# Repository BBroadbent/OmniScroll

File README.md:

# OmniScroll

**OmniScroll** is an open-source, ultra-smooth desktop scroll wheel designed for precise CAD navigation, timeline scrub control, and high-speed document scrolling. 

By utilizing a large-diameter thin-section bearing and an off-axis magnetic rotary encoder, FluxDial achieves an effortless flywheel spin with zero axis wobble.

---

## Key Features

* **Flywheel Momentum:** Utilizes an `S6808` hybrid ceramic bearing ($40 \times 52 \times 7\text{ mm}$) stripped of grease for near-zero rotational resistance.
* **Magnetic Angle Sensing:** High-resolution rotary encoder (AS5600 / MA730) for smooth, non-contact position tracking.
* **Zero Axis Play:** Large-bore thin-section design houses internal electronics inside the hollow core, lowering the center of gravity and eliminating side-to-side wobble.
* **Custom Control Curves:** Configurable firmware supporting variable-speed scroll acceleration, granular scrub modes, and custom macro actions.

---

## Hardware Assembly

### Bill of Materials (BOM)

| Component | Specification / Part | Qty | Notes |
| :--- | :--- | :--- | :--- |
| **Main Bearing** | `S6808-2RS` Hybrid Ceramic ($40 \times 52 \times 7\text{ mm}$) | 1 | Degreased with IPA for maximum free-spin |
| **Magnetic Encoder** | AS5600 or MA730 PCB Module | 1 | Mounts coaxially inside the inner ring |
| **Diametral Magnet** | $6\text{ mm} \times 2.5\text{ mm}$ N35 (Diametrically Magnetized) | 1 | Fixed to the rotating outer knob shaft |
| **Microcontroller** | Raspberry Pi Pico / Seeed XIAO (RP2040) | 1 | Compact form factor fits inside housing base |
| **Enclosure** | 3D Printed (PLA/PETG) or Machined Aluminum | 1 | Files provided in `/cad` |

---

## Getting Started

### 1. Bearing Preparation
1. Carefully pop off the rubber seals (`2RS`) on the `S6808` bearing.
2. Submerge in isopropyl alcohol (IPA) and spin thoroughly to strip factory grease.
3. Blow dry with compressed air. (Optional: Apply 1 drop of high-speed instrument oil for quieter operation).

### 2. Firmware Setup
1. Clone this repository:
   ```bash
   git clone [https://github.com/your-username/FluxDial.git](https://github.com/your-username/FluxDial.git)

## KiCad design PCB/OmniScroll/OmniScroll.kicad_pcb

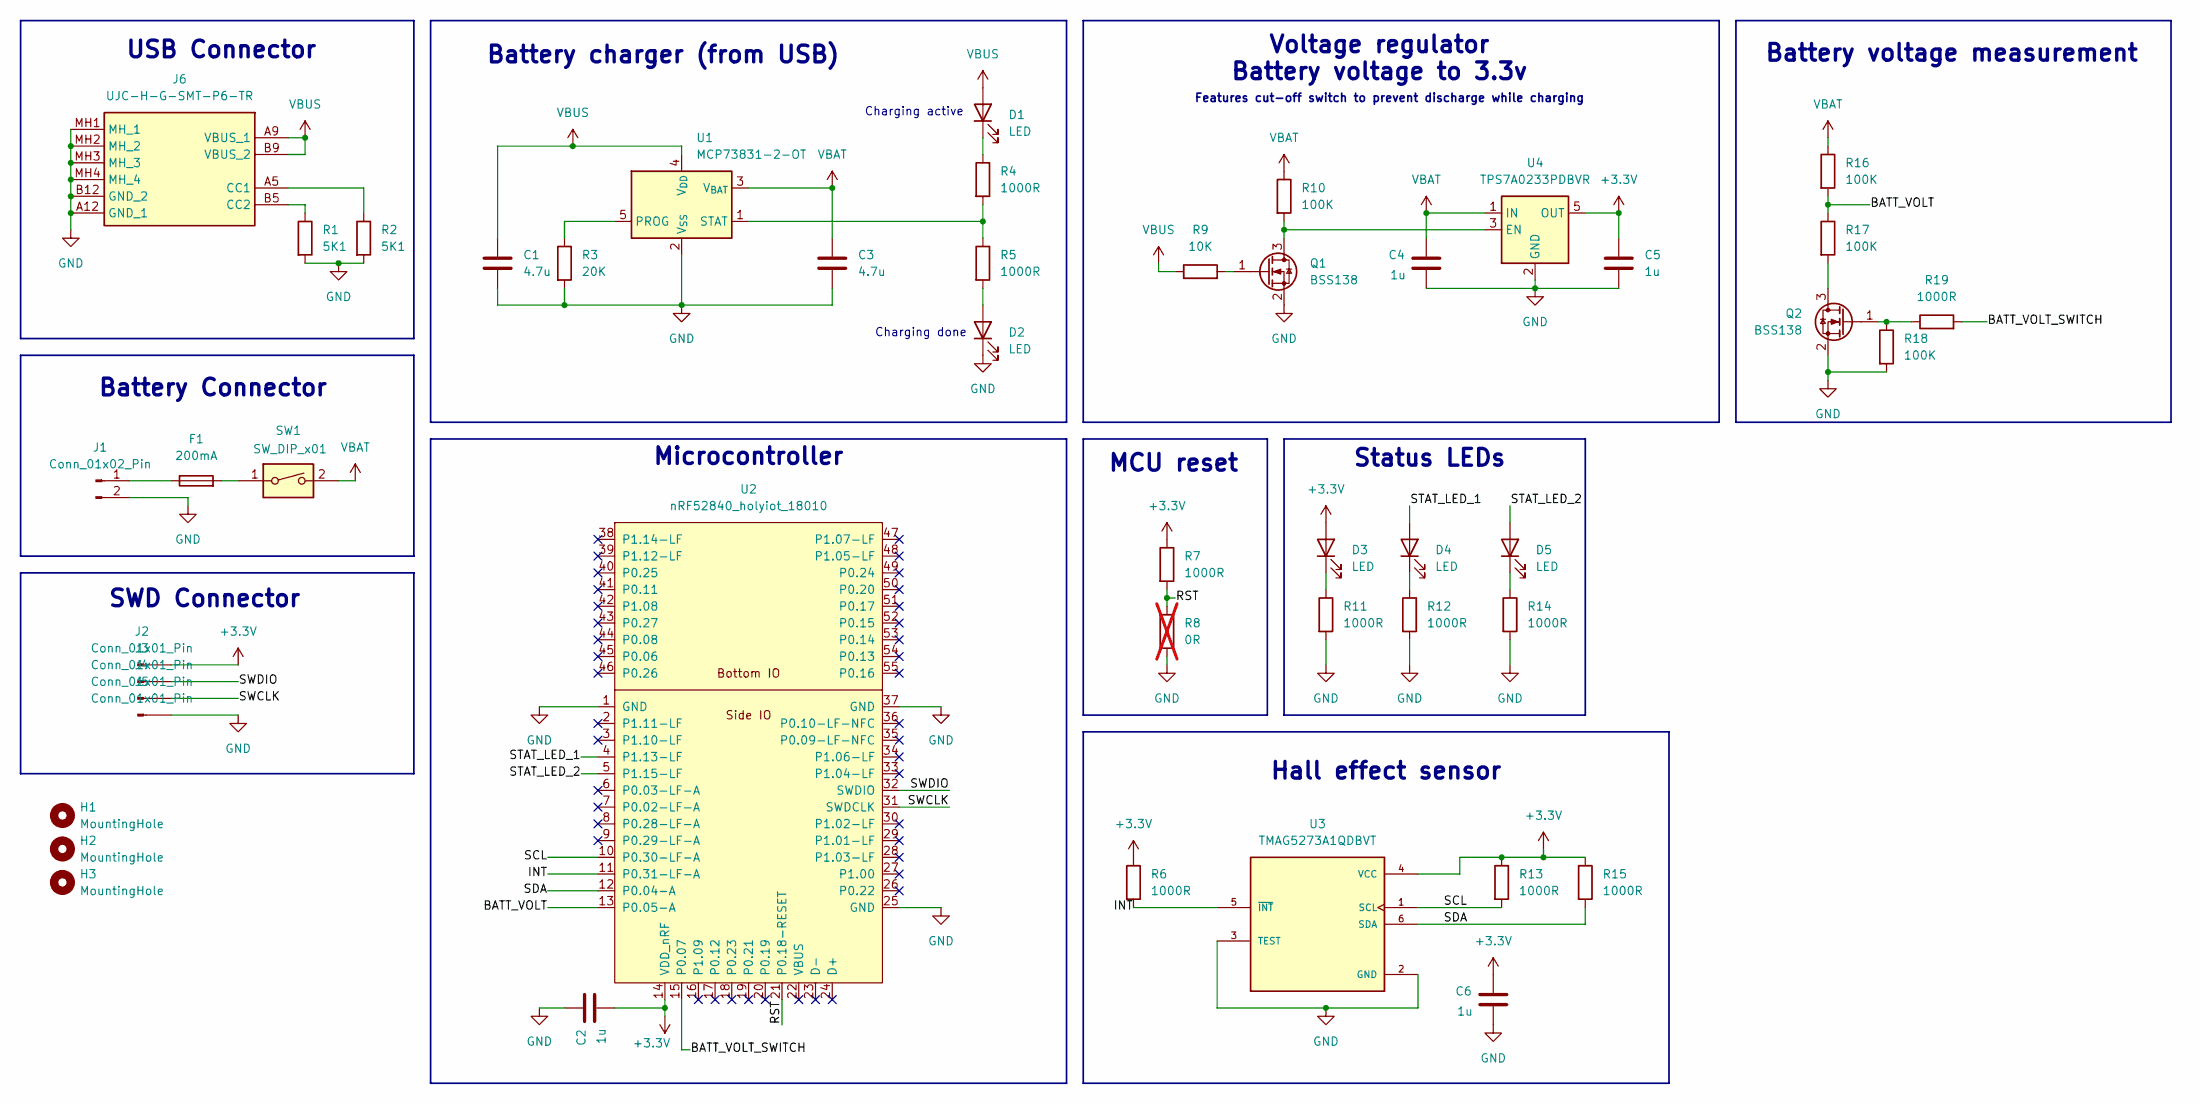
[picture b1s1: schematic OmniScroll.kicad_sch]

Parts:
C1, C3: 4.7u; C_0603_1608Metric_Pad1.08x0.95mm_HandSolder
C2, C4, C5, C6: 1u; C_0603_1608Metric_Pad1.08x0.95mm_HandSolder
D1, D2, D3, D4, D5: LED; LED_0603_1608Metric_Pad1.05x0.95mm_HandSolder
F1: 200mA; R_0603_1608Metric_Pad0.98x0.95mm_HandSolder
H1, H2, H3: MountingHole; MountingHole_2.2mm_M2_DIN965_Pad
J1: Conn_01x02_Pin; Molex_PicoBlade_53048-0210_1x02_P1.25mm_Horizontal
J2, J3, J4, J5: Conn_01x01_Pin; TestPoint_Pad_D1.5mm
J6: UJC-H-G-SMT-P6-TR; UJCHGSMTP6TR; Manufacturer_Part_Number UJC-H-G-SMT-P6-TR; Mouser Part Number 179-UJCHGSMTP6TR
Q1, Q2: BSS138; SOT-23
R1, R2: 5K1; R_0603_1608Metric_Pad0.98x0.95mm_HandSolder
R3: 20K; R_0603_1608Metric_Pad0.98x0.95mm_HandSolder
R4, R5, R6, R7, R11, R12, R13, R14, R15, R19: 1000R; R_0603_1608Metric_Pad0.98x0.95mm_HandSolder
R8: 0R; R_0402_1005Metric_Pad0.72x0.64mm_HandSolder; not fitted
R9: 10K; R_0603_1608Metric_Pad0.98x0.95mm_HandSolder
R10, R16, R17, R18: 100K; R_0603_1608Metric_Pad0.98x0.95mm_HandSolder
SW1: SW_DIP_x01; SW_DIP_SPSTx01_Slide_6.7x4.1mm_W8.61mm_P2.54mm_LowProfile
U1: MCP73831-2-OT; SOT-23-5
U2: nRF52840_holyiot_18010
U3: TMAG5273A1QDBVT; SOT95P280X140-6N; PARTREV B
U4: TPS7A0233PDBVR; SOT-23-5

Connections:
+3.3V: C2.2, C5.1, C6.1, D3.2 (A), J2.1 (Pin_1_1), R6.1, R7.1, R13.1, R15.1, U2.14 (VDD_nRF), U3.4 (VCC), U4.5 (OUT)
/BATT_VOLT: R16.2, R17.1, U2.13 (P0.05-A)
/BATT_VOLT_SWITCH: R19.2, U2.15 (P0.07)
/INT: R6.2, U2.11 (P0.31-LF-A), U3.5 (~INT)
/RST: R7.2, R8.1, U2.21 (P0.18-RESET)
/SCL: R13.2, U2.10 (P0.30-LF-A), U3.1 (SCL)
/SDA: R15.2, U2.12 (P0.04-A), U3.6 (SDA)
/STAT_LED_1: D4.2 (A), U2.4 (P1.13-LF)
/STAT_LED_2: D5.2 (A), U2.5 (P1.15-LF)
/SWCLK: J4.1 (Pin_1_1), U2.31 (SWDCLK)
/SWDIO: J3.1 (Pin_1_1), U2.32 (SWDIO)
GND: C1.2, C2.1, C3.2, C4.2, C5.2, C6.2, D2.1 (K), J1.2, J5.1 (Pin_1_1), J6.A12 (GND_1), J6.B12 (GND_2), J6.MH1 (MH_1), J6.MH2 (MH_2), J6.MH3 (MH_3), J6.MH4 (MH_4), Q1.2 (S), Q2.2 (S), R1.2, R2.2, R3.2, R8.2, R11.2, R12.2, R14.2, R18.2, U1.2 (V_{SS}), U2.1 (GND), U2.25 (GND), U2.37 (GND), U3.2 (GND), U3.3 (TEST), U4.2 (GND)
unnamed: D1.1 (K), R4.1
unnamed: D2.2 (A), R5.2
unnamed: D3.1 (K), R11.1
unnamed: D4.1 (K), R12.1
unnamed: D5.1 (K), R14.1
unnamed: F1.2, SW1.1
unnamed: F1.1, J1.1
unnamed: J6.A5 (CC1), R2.1
unnamed: J6.B5 (CC2), R1.1
unnamed: Q1.3 (D), R10.2, U4.3 (EN)
unnamed: Q1.1 (G), R9.2
unnamed: Q2.3 (D), R17.2
unnamed: Q2.1 (G), R18.1, R19.1
unnamed: R3.1, U1.5 (PROG)
unnamed: R4.2, R5.1, U1.1 (STAT)
VBAT: C3.1, C4.1, R10.1, R16.1, SW1.2, U1.3 (V_{BAT}), U4.1 (IN)
VBUS: C1.1, D1.2 (A), J6.A9 (VBUS_1), J6.B9 (VBUS_2), R9.1, U1.4 (V_{DD})

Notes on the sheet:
Status LEDs
MCU reset
SWD Connector
Microcontroller
Battery voltage measurement
USB Connector
Hall effect sensor
Charging done
Charging active
Battery charger (from USB)
Voltage regulator Battery voltage to 3.3v
Battery Connector
Features cut-off switch to prevent discharge while charging

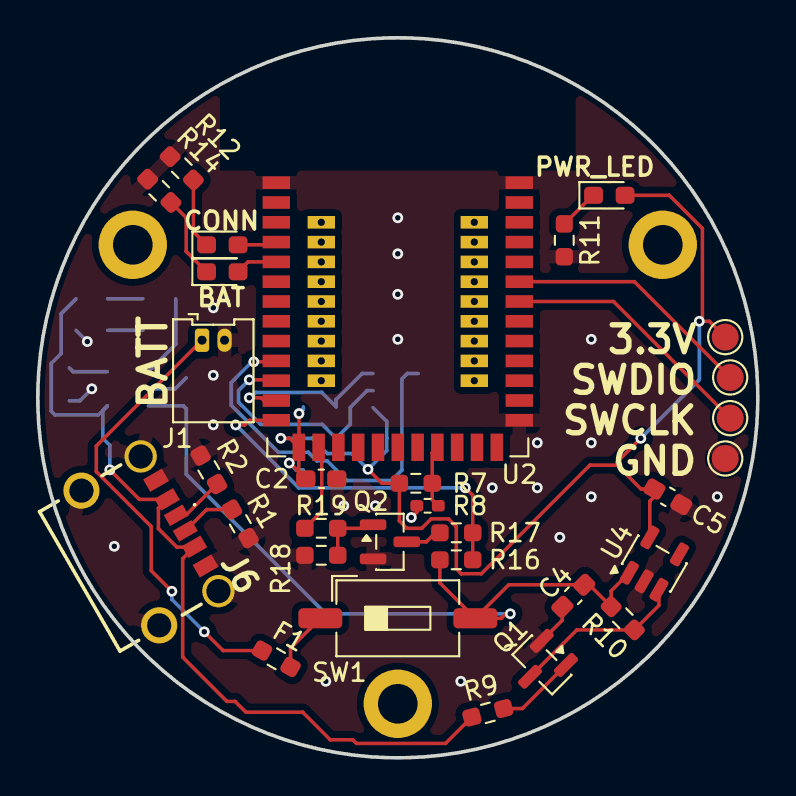
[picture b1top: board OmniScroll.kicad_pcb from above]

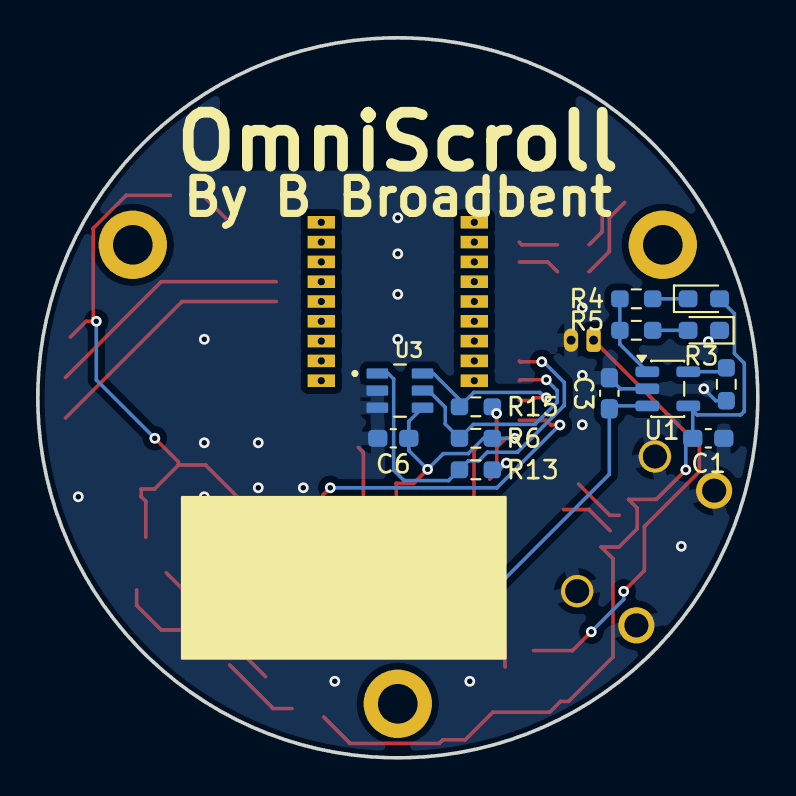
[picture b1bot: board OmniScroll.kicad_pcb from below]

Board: 2 copper layers, 40.0 x 40.0 mm, 47 parts (13 on the bottom side), 29 nets.
